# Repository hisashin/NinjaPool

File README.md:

NinjaPool
=========

Opensource(GPL) Electrophoresis machine.

Photos https://www.facebook.com/hisakawa/media_set?set=a.10151899612689481.1073741833.663784480&type=3

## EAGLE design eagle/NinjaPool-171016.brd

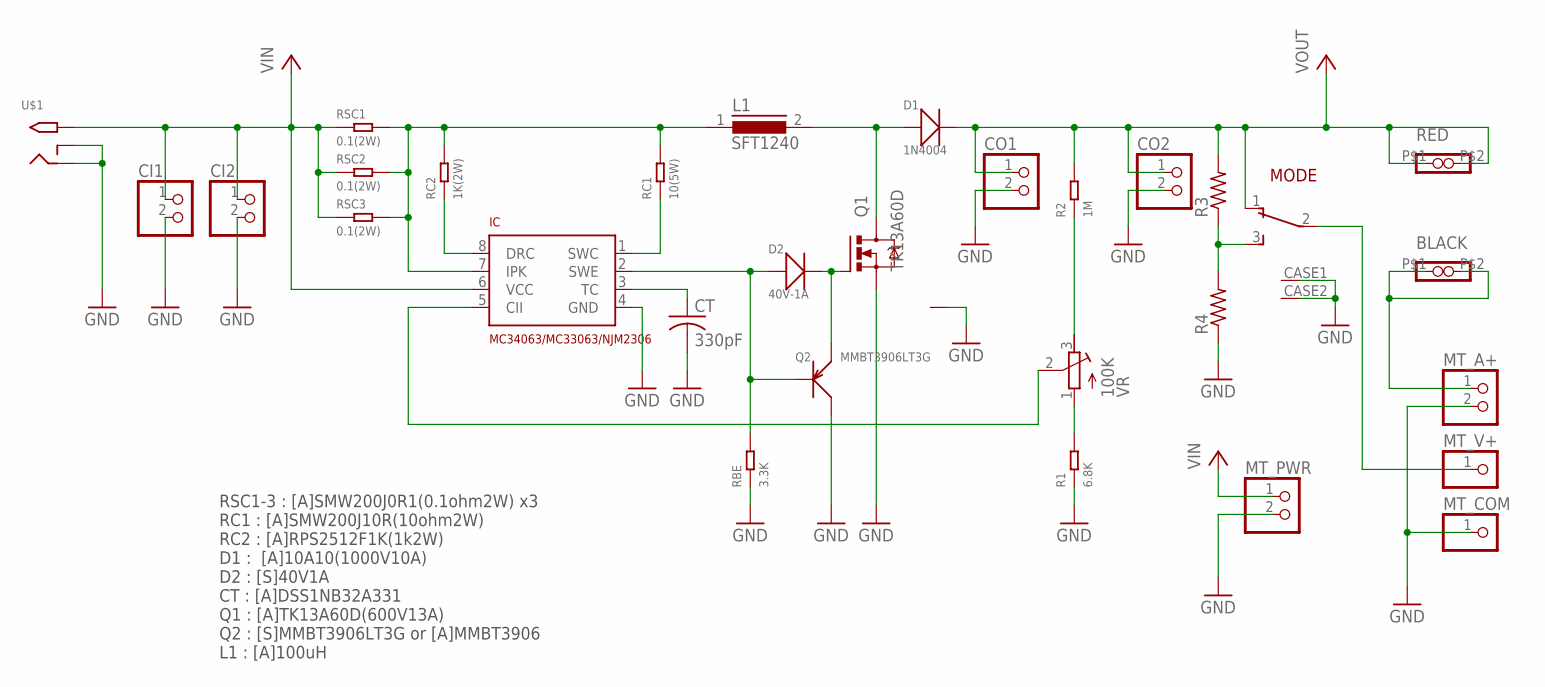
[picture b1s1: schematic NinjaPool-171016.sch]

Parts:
BLACK: BANANA1; BANANA
CI1, CI2: PINHD-1X2; 1X02
CO1, CO2: PINHD-1X2; 1X02
CT: 330pF; C050-024X044
D1: 1N4004; DO-41
D2: 40V-1A; DO-214AC
HEAT: HEAT111PB015; HEAT11PB015
IC: MC34063/MC33063/NJM2306; DIL8
L1: SFT1240
MODE: 4MS1R202M6QES
MT_A+: PINHD-1X2; 1X02
MT_COM: PINHD-1X1; 1X01
MT_PWR: PINHD-1X2; 1X02
MT_V+: PINHD-1X1; 1X01
Q1: TK13A60D; TO220BV
Q2: MMBT3906LT3G; SOT-23
R1: 6.8K; R0603
R2: 1M; R0603
R3, R4: R-US_R0603; R0603
RBE: 3.3K; R0603
RC1: 10(5W); SWE500
RC2: 1K(2W); R2512
RED: BANANA1; BANANA
RSC1, RSC2, RSC3: 0.1(2W); SMW200
U$1: 2.1MMJACKTHM; PJ-102A
VR: 100K; AITENDO_R16K1

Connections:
A+: BLACK.P$1 (1), BLACK.P$2 (2), MT_A+.1
GND: CI1.2, CI2.2, CO1.2, CO2.2, CT.2, HEAT.P$1, IC.4 (GND), MODE.CASE1, MODE.CASE2, MT_A+.2, MT_COM.1, MT_PWR.2, Q1.S, Q2.3 (C), R1.1, R4.1, RBE.1, U$1.RING, U$1.RING_SW
LIN: IC.7 (IPK), L1.1, RC1.2, RC2.2, RSC1.2, RSC2.2, RSC3.2
unnamed: R2.1, VR.3 (E)
unnamed: IC.8 (DRC), RC2.1
unnamed: IC.1 (SWC), RC1.1
unnamed: CT.1, IC.3 (TC)
unnamed: MODE.3, R3.1, R4.2
unnamed: R1.2, VR.1 (A)
unnamed: IC.5 (CII), VR.2 (S)
unnamed: MODE.2, MT_V+.1
Q1_DRAIN: D1.1 (+), L1.2, Q1.D
Q1_GATE_Q2_COLLECT: D2.2 (-), Q1.G, Q2.2 (E)
Q2_BASE: D2.1 (+), IC.2 (SWE), Q2.1 (B), RBE.2
VIN: CI1.1, CI2.1, IC.6 (VCC), MT_PWR.1, RSC1.1, RSC2.1, RSC3.1, U$1.TIP
VOUT: CO1.1, CO2.1, D1.2 (-), MODE.1, R2.2, R3.2, RED.P$1 (1), RED.P$2 (2)

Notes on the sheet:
RSC1-3 : [A]SMW200J0R1(0.1ohm2W) x3 RC1 : [A]SMW200J10R(10ohm2W) RC2 : [A]RPS2512F1K(1k2W) D1 : [A]10A10(1000V10A) D2 : [S]40V1A CT : [A]DSS1NB32A331 Q1 : [A]TK13A60D(600V13A) Q2 : [S]MMBT3906LT3G or [A]MMBT3906 L1 : [A]100uH

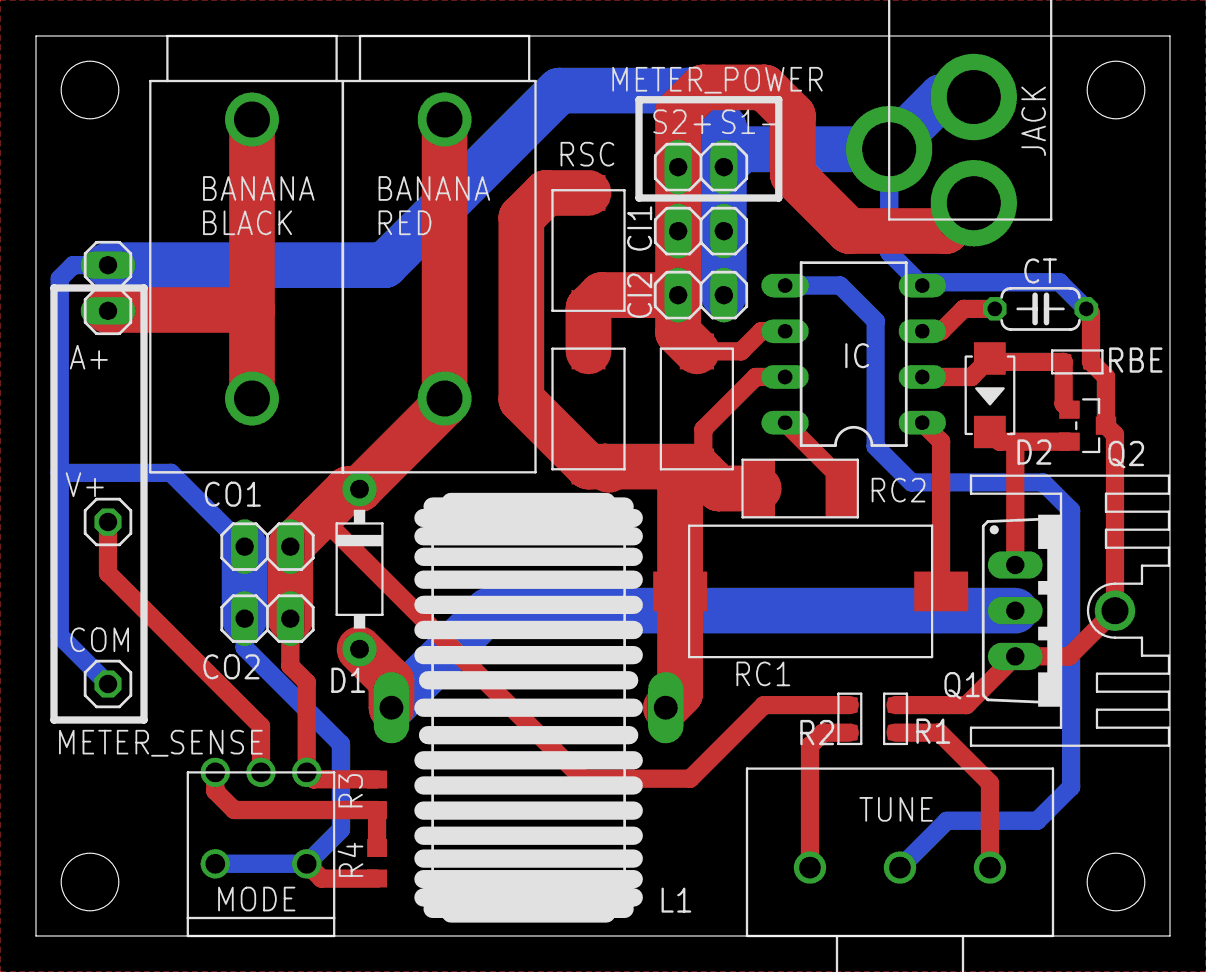
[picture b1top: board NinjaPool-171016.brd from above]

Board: 2 copper layers, 63.0 x 50.0 mm, 32 parts (1 on the bottom side), 16 nets.

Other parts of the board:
U$3: TORI_0.5

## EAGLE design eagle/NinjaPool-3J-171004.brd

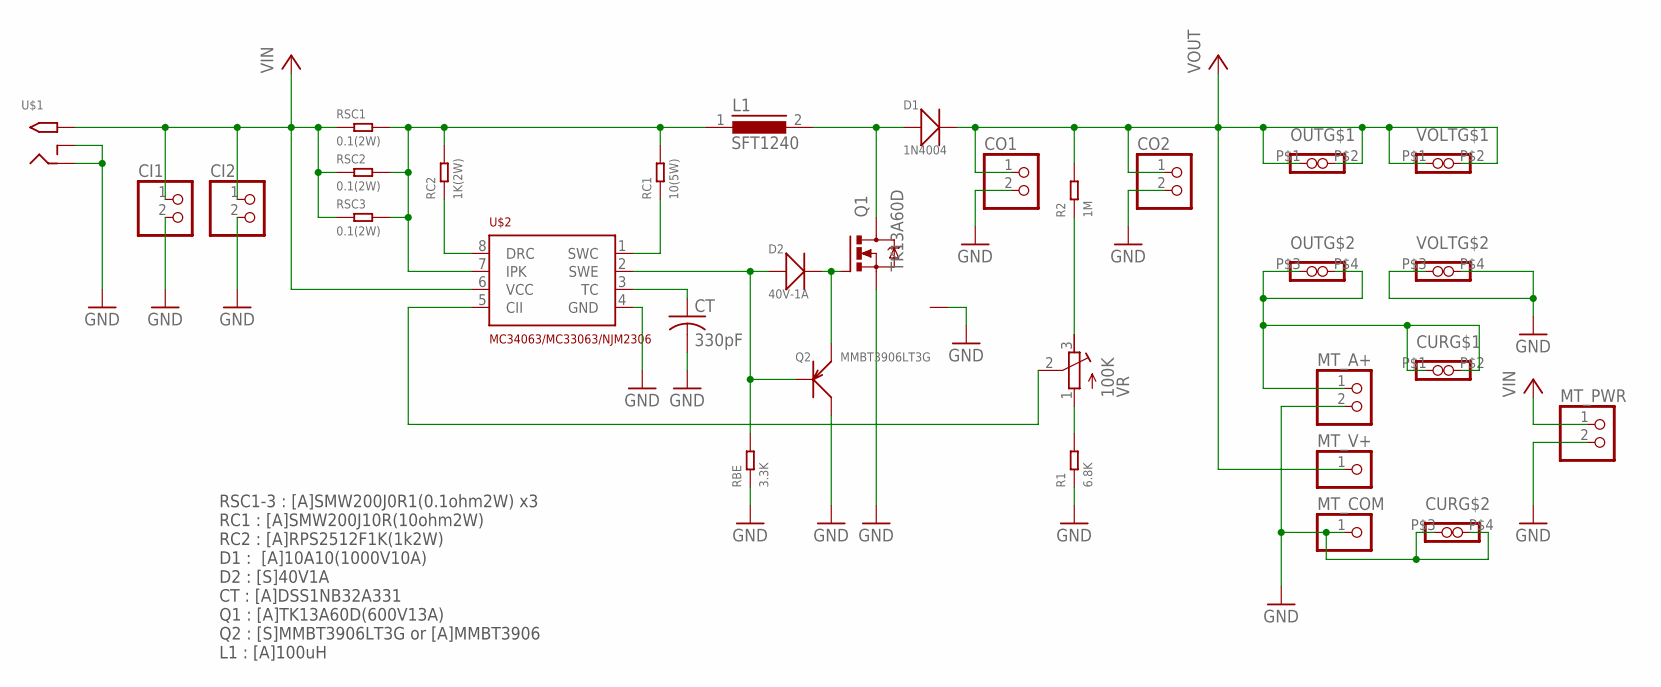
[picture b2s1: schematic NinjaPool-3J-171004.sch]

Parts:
CI1, CI2: PINHD-1X2; 1X02
CO1, CO2: PINHD-1X2; 1X02
CT: 330pF; C050-024X044
CUR: BANANA; BANANA_TMP
D1: 1N4004; DO-41
D2: 40V-1A; DO-214AC
HEAT: HEAT111PB015; HEAT11PB015
L1: SFT1240
MT_A+: PINHD-1X2; 1X02
MT_COM: PINHD-1X1; 1X01
MT_PWR: PINHD-1X2; 1X02
MT_V+: PINHD-1X1; 1X01
OUT: BANANA; BANANA_TMP
Q1: TK13A60D; TO220BV
Q2: MMBT3906LT3G; SOT-23
R1: 6.8K; R0603
R2: 1M; R0603
RBE: 3.3K; R0603
RC1: 10(5W); SWE500
RC2: 1K(2W); R2512
RSC1, RSC2, RSC3: 0.1(2W); SMW200
U$1: 2.1MMJACKTHM; PJ-102A
U$2: MC34063/MC33063/NJM2306; DIL8
VOLT: BANANA; BANANA_TMP
VR: 100K; AITENDO_R16K1

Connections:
A+: CUR.P$1 (1), CUR.P$2 (2), MT_A+.1, OUT.P$3 (1), OUT.P$4 (2)
GND: CI1.2, CI2.2, CO1.2, CO2.2, CT.2, CUR.P$3 (1), CUR.P$4 (2), HEAT.P$1, MT_A+.2, MT_COM.1, MT_PWR.2, Q1.S, Q2.3 (C), R1.1, RBE.1, U$1.RING, U$1.RING_SW, U$2.4 (GND), VOLT.P$3 (1), VOLT.P$4 (2)
LIN: L1.1, RC1.2, RC2.2, RSC1.2, RSC2.2, RSC3.2, U$2.7 (IPK)
unnamed: R2.1, VR.3 (E)
unnamed: RC2.1, U$2.8 (DRC)
unnamed: RC1.1, U$2.1 (SWC)
unnamed: CT.1, U$2.3 (TC)
unnamed: R1.2, VR.1 (A)
unnamed: U$2.5 (CII), VR.2 (S)
Q1_DRAIN: D1.1 (+), L1.2, Q1.D
Q1_GATE_Q2_COLLECT: D2.2 (-), Q1.G, Q2.2 (E)
Q2_BASE: D2.1 (+), Q2.1 (B), RBE.2, U$2.2 (SWE)
VIN: CI1.1, CI2.1, MT_PWR.1, RSC1.1, RSC2.1, RSC3.1, U$1.TIP, U$2.6 (VCC)
VOUT: CO1.1, CO2.1, D1.2 (-), MT_V+.1, OUT.P$1 (1), OUT.P$2 (2), R2.2, VOLT.P$1 (1), VOLT.P$2 (2)

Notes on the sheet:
RSC1-3 : [A]SMW200J0R1(0.1ohm2W) x3 RC1 : [A]SMW200J10R(10ohm2W) RC2 : [A]RPS2512F1K(1k2W) D1 : [A]10A10(1000V10A) D2 : [S]40V1A CT : [A]DSS1NB32A331 Q1 : [A]TK13A60D(600V13A) Q2 : [S]MMBT3906LT3G or [A]MMBT3906 L1 : [A]100uH

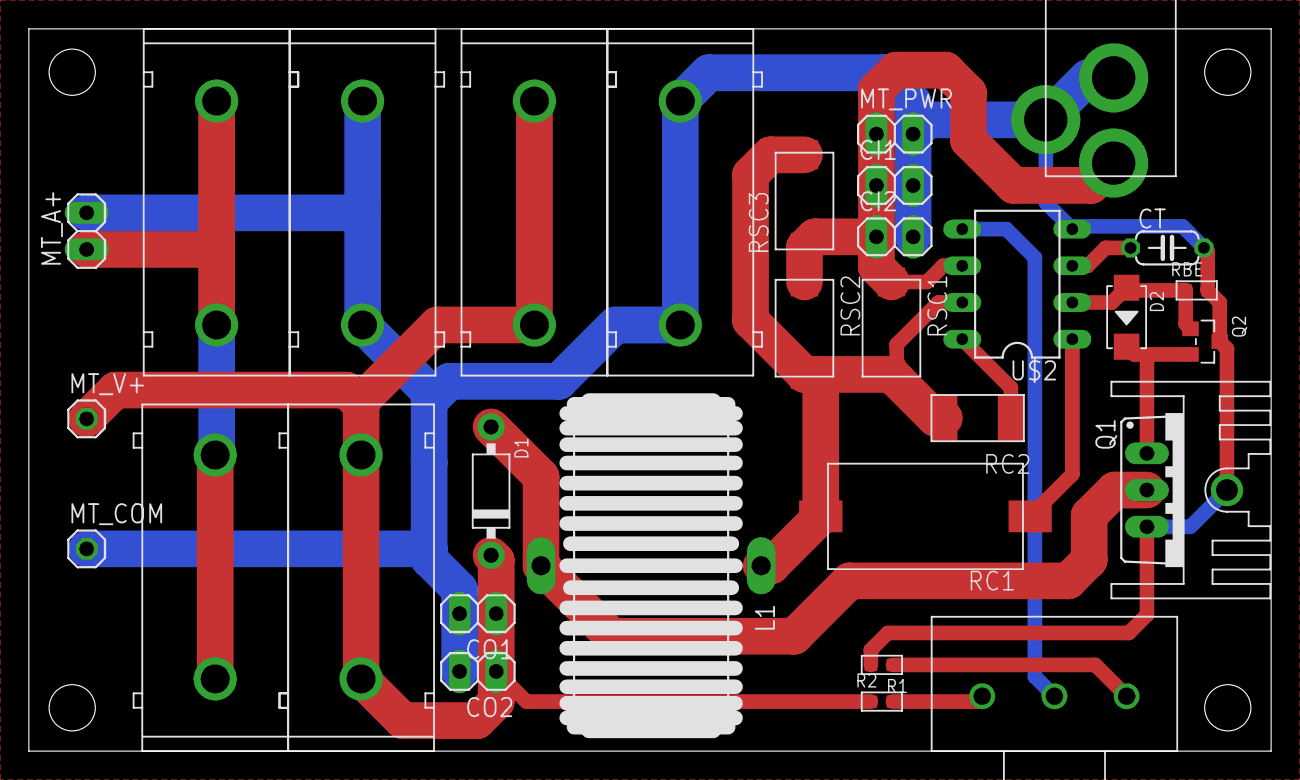
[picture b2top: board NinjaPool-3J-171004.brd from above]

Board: 2 copper layers, 86.0 x 50.0 mm, 30 parts (1 on the bottom side), 14 nets.

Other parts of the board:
U$3: TORI_0.5

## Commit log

2013-10-11 starting project
2013-10-14 it's GPL!
2013-10-14 add logo
2013-11-06 add gel tray and comb roughly
2013-11-09 add corner image
2013-11-12 update geltray
2013-11-12 add lifter
2013-11-12 almost done updating
2013-11-12 body done.need patent check about its cover
2013-11-12 designing cover
2013-11-13 avoid patent conflict
2013-11-14 updates to cut
2017-10-03 adding pcb
2017-10-09 ordered pcb
2017-10-16 fixing things
